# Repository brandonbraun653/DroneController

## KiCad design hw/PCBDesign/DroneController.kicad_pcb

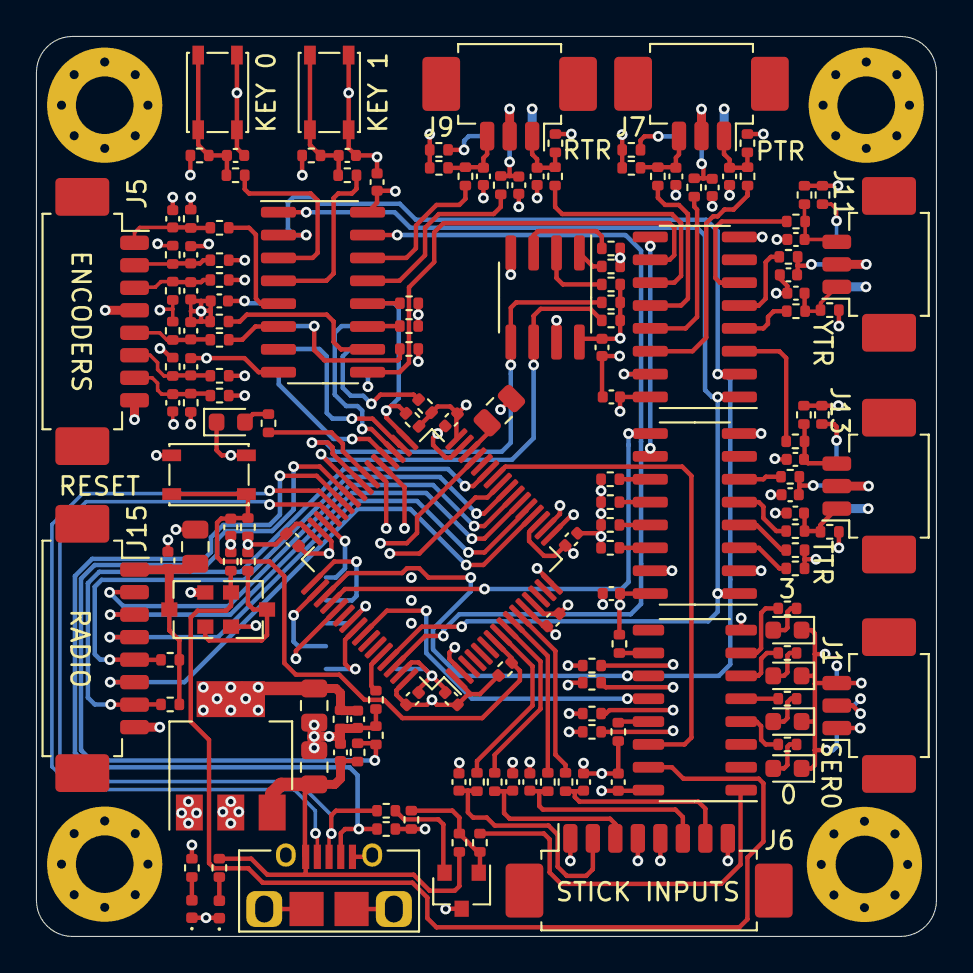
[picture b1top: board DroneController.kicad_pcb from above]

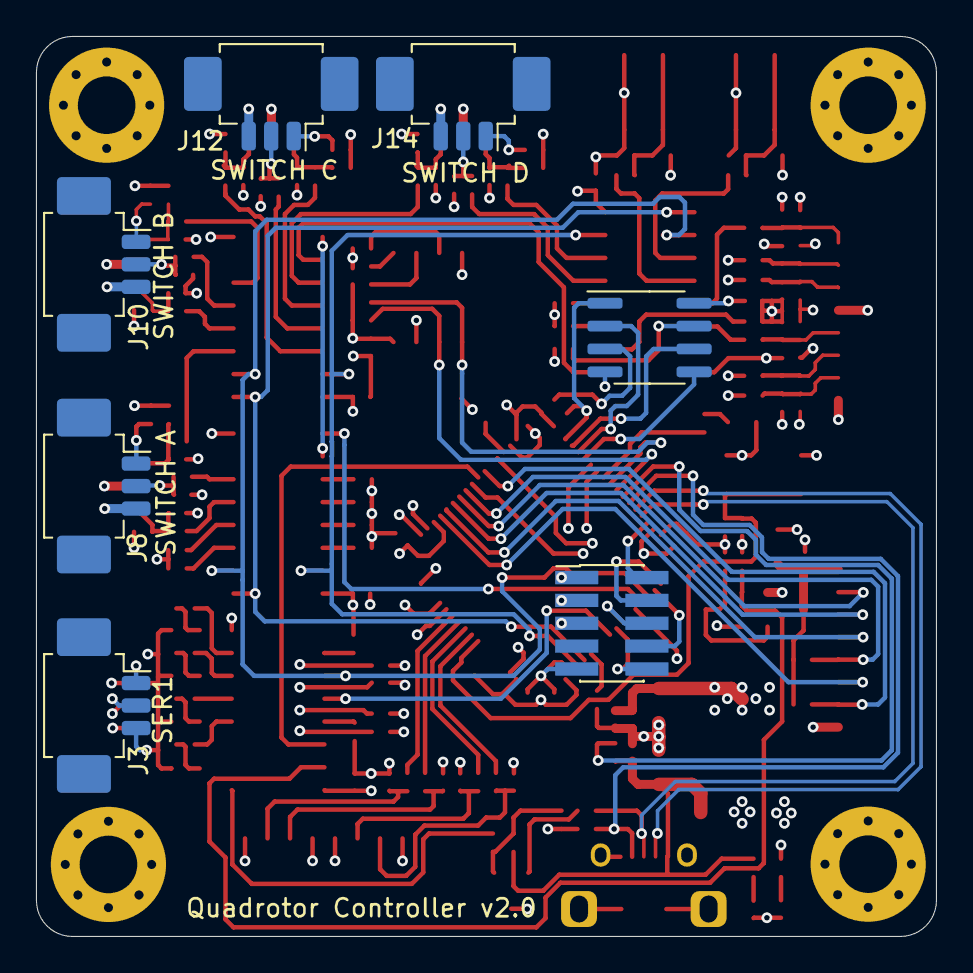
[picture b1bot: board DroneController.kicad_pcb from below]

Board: 4 copper layers, 50.0 x 50.0 mm, 173 parts (7 on the bottom side), 129 nets.

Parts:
C1, C2, C3, C10, C11, C12, C13, C14, C15, C16, C17, C18, C19, C20, C21, C26, C27, C28, C29, C30, C31, C32, C33, C35, C37, C47, C50, C55, C56, C57: 100n; C_0402_1005Metric
C4, C5, C6, C7, C8, C9, C22, C23, C24, C25: 10n; C_0402_1005Metric
C34: 10uF; C_0805_2012Metric
C41, C44: 1uF; C_0805_2012Metric
C52: 2.2uF; C_0805_2012Metric
D1: DBG_LED_0; LED_0603_1608Metric
D3: STATUS_LED; LED_0603_1608Metric
D4: DBG_LED_3; LED_0603_1608Metric
D5: DBG_LED_2; LED_0603_1608Metric
D6: DBG_LED_1; LED_0603_1608Metric
D8: LED_5V0; LED_0402_1005Metric
D9: LED_3V3; LED_0402_1005Metric
H1, H2, H3, H4: MountingHole_Pad; MountingHole_3.2mm_M3_Pad_Via
J1, J3: SerialDebug; Molex_PicoBlade_53261-0371_1x03-1MP_P1.25mm_Horizontal
J2: USB_B_Micro; Amphenol-MicroB
J4: Conn_ARM_JTAG_SWD_10; PinHeader_2x05_P1.27mm_Vertical_SMD
J5: EncoderConn; Molex_PicoBlade_53261-0871_1x08-1MP_P1.25mm_Horizontal
J6: JoystickConn; Molex_PicoBlade_53261-0871_1x08-1MP_P1.25mm_Horizontal
J7: PTrim; Molex_PicoBlade_53261-0371_1x03-1MP_P1.25mm_Horizontal
J8: SW_A; Molex_PicoBlade_53261-0371_1x03-1MP_P1.25mm_Horizontal
J9: RTrim; Molex_PicoBlade_53261-0371_1x03-1MP_P1.25mm_Horizontal
J10: SW_B; Molex_PicoBlade_53261-0371_1x03-1MP_P1.25mm_Horizontal
J11: YTrim; Molex_PicoBlade_53261-0371_1x03-1MP_P1.25mm_Horizontal
J12: SW_C; Molex_PicoBlade_53261-0371_1x03-1MP_P1.25mm_Horizontal
J13: TTrim; Molex_PicoBlade_53261-0371_1x03-1MP_P1.25mm_Horizontal
J14: SW_D; Molex_PicoBlade_53261-0371_1x03-1MP_P1.25mm_Horizontal
J15: Conn_01x08; Molex_PicoBlade_53261-0871_1x08-1MP_P1.25mm_Horizontal
Q2: MMBT3904; SOT-23
Q3: 2N7002; SOT-23
Q5: LBSS84LT1G; SOT-23
R1, R2, R7, R8, R9, R10, R11, R12, R15, R17, R20, R22, R23, R24, R28, R29, R30, R34, R35, R36, R45, R46, R47, R49, R50, R51, R52, R53, R54, R57, R58, R59, R61, R62, R64, R65, R66, R67, R70, R71, R72, R74, R85, R88, R89, R90, R91, R96, R97, R98, R99: 10k; R_0402_1005Metric
R3, R4, R5, R6, R13, R14, R16, R18, R19, R21, R25, R26, R27, R31, R32, R33, R37, R38, R39, R40, R41, R42, R48, R55: 1k; R_0402_1005Metric
R56, R92, R93, R94, R95: 560; R_0402_1005Metric
R60, R68, R69, R75: 1.5k; R_0402_1005Metric
R63: 330; R_0402_1005Metric
R73: 5.1k; R_0402_1005Metric
R76: 4.7k; R_0402_1005Metric
R77: 33k; R_0402_1005Metric
R78: 100; R_0402_1005Metric
SW13: Key_User; SW_SPST_PTS810
SW15: Key_nRESET; SW_SPST_PTS810
SW17: Key_nBOOT; SW_SPST_PTS810
U1, U2, U3: 74HC165; SOIC-16_3.9x9.9mm_P1.27mm
U4: AT25SF081; SOIC-8_3.9x4.9mm_P1.27mm
U5: AT24C256; SOIC-8_3.9x4.9mm_P1.27mm
U8: AMS1117-3.3; SOT-223-3_TabPin2
U11: 74HC595; SO-16_3.9x9.9mm_P1.27mm
U13: STM32F446RETx; LQFP-64_10x10mm_P0.5mm

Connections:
+3V3: C1.1, C2.1, C3.1, C26.1, C27.1, C29.1, C31.1, C33.1, C44.1, C47.1, C50.1, C55.1, C56.1, C57.1, J4.1, J6.1, J6.5, Q2.3, Q5.2, R7.1, R8.2, R9.1, R10.2, R11.1, R12.1, R15.1, R17.1, R20.1, R22.1, R23.1, R24.1, R28.1, R29.1, R30.1, R34.1, R35.1, R36.1, R50.1, R53.1, R57.1, R62.1, R63.2, R64.1, R67.1, R68.1, R69.1, R85.1, R88.2, R97.2, R98.2, R99.1, U1.16, U2.16, U3.16, U4.8, U5.8, U8.2, U11.16, U13.1, U13.13, U13.19, U13.32, U13.48, U13.64
+5V: C37.1, C41.2, J2.1, R60.2, R73.2, R76.2, U8.3
/Human Machine Interface/ENC0_A: R5.2, U13.53
/Human Machine Interface/ENC0_B: R6.2, U13.2
/Human Machine Interface/ENC1_A: R3.2, U13.16
/Human Machine Interface/ENC1_B: R4.2, U13.17
/Human Machine Interface/Joy Stick Inputs/JS_0: C25.1, J6.2, R42.1
/Human Machine Interface/Joy Stick Inputs/JS_1: C24.1, J6.3, R41.2
/Human Machine Interface/Joy Stick Inputs/JS_2: C23.1, J6.6, R40.1
/Human Machine Interface/Joy Stick Inputs/JS_3: C22.1, J6.7, R39.2
/Human Machine Interface/KEY_MISO: U1.9, U13.52
/Human Machine Interface/KEY_SCK: U1.2, U2.2, U3.2, U11.11, U13.51
/Human Machine Interface/KEY_nCS: U1.15, U2.15, U3.15, U13.62
/Human Machine Interface/KEY_nSAMPLE: U1.1, U2.1, U3.1, U13.61
/Human Machine Interface/Rotary Encoder/SW1_A: C4.2, J5.2, R3.1, R7.2
/Human Machine Interface/Rotary Encoder/SW1_B: C5.1, J5.3, R4.1, R8.1
/Human Machine Interface/Rotary Encoder/SW1_Btn: C8.1, J5.1, R11.2, R13.2
/Human Machine Interface/Rotary Encoder/SW2_A: C6.2, J5.6, R5.1, R9.2
/Human Machine Interface/Rotary Encoder/SW2_B: C7.1, J5.7, R6.1, R10.1
/Human Machine Interface/Rotary Encoder/SW2_Btn: C9.1, J5.5, R12.2, R14.2
/Human Machine Interface/d0: R54.1, U3.11
/Human Machine Interface/d1: R52.1, U3.12
/Human Machine Interface/d2: R33.2, U3.13
/Human Machine Interface/d3: R25.1, U3.14
/Human Machine Interface/d4: R48.2, U3.3
/Human Machine Interface/d5: R55.2, U3.4
/Human Machine Interface/d6: R13.1, U3.5
/Human Machine Interface/d7: R14.1, U3.6
/Human Machine Interface/d8: R26.2, U2.11
/Human Machine Interface/d9: R18.1, U2.12
/Human Machine Interface/d10: R27.2, U2.13
/Human Machine Interface/d11: R19.2, U2.14
/Human Machine Interface/d12: R37.1, U2.3
/Human Machine Interface/d13: R32.2, U2.4
/Human Machine Interface/d14: R21.2, U2.5
/Human Machine Interface/d15: R31.1, U2.6
/Human Machine Interface/d16: R49.1, U1.11
/Human Machine Interface/d17: R2.1, U1.12
/Human Machine Interface/d18: R47.1, U1.13
/Human Machine Interface/d19: R51.1, U1.14
/Human Machine Interface/d20: R46.1, U1.3
/Human Machine Interface/d21: R45.1, U1.4
/Human Machine Interface/d22: R38.2, U1.5
/Human Machine Interface/d23: R16.2, U1.6
/Human Machine Interface/nRESET: C30.2, R53.2, R97.1, SW15.1, U13.7
/Power Supply/USB_D+: J2.3, R75.1, U13.45
/Power Supply/USB_D-: J2.2, U13.44
/Power Supply/USB_ID: J2.4, R72.2, U13.43
/Processor/ANALOG_IN_VPITCH: R40.2, U13.10
/Processor/ANALOG_IN_VROLL: R39.1, U13.11
/Processor/ANALOG_IN_VTHROTTLE: R42.2, U13.8
/Processor/ANALOG_IN_VYAW: R41.1, U13.9
/Processor/DBG_UART_RX_0: J1.2, R89.2
/Processor/DBG_UART_RX_1: J3.2, R59.2
/Processor/DBG_UART_TX_0: J1.1, R91.1
/Processor/DBG_UART_TX_1: J3.1, R65.2
/Processor/EEPROM_SCL: R69.2, U5.6, U13.41
/Processor/EEPROM_SDA: R68.2, U5.5, U13.40
/Processor/JT_TCK: J4.4, U13.49
/Processor/JT_TDI: J4.8, U13.50
/Processor/JT_TDO: J4.6, U13.55
/Processor/JT_TMS: J4.2, U13.46
/Processor/JT_nRST: J4.10, U13.56
/Processor/KEY_MOSI: U11.14, U13.26
/Processor/KeyOut_nCS: U11.12, U13.57
/Processor/NOR_MISO: U4.2, U13.35
/Processor/NOR_MOSI: U4.5, U13.36
/Processor/NOR_SCK: U4.6, U13.34
/Processor/NOR_nCS: R99.2, U4.1, U13.33
/Processor/RF24_CE: J15.6, U13.20
/Processor/RF24_MISO: J15.3, U13.22
/Processor/RF24_MOSI: J15.2, U13.23
/Processor/RF24_SCK: J15.4, U13.21
/Processor/RF24_VCC_EN: Q3.1, R58.2, U11.15
/Processor/RF24_nCS: J15.5, R70.2, U13.24
/Processor/RF24_nIRQ: J15.7, R71.2, U13.27
/Processor/USB_SENSE: R73.1, R74.2, U13.42
/Processor/USB_nRENUMERATE: R78.1, U11.1
GND: C1.2, C2.2, C3.2, C4.1, C5.2, C6.1, C7.2, C8.2, C9.2, C10.2, C11.2, C12.2, C13.2, C14.2, C15.2, C16.2, C17.2, C18.2, C19.2, C20.2, C21.2, C22.2, C23.2, C24.2, C25.2, C26.2, C27.2, C28.1, C29.2, C30.1, C31.2, C32.1, C33.2, C34.2, C35.2, C37.2, C41.1, C44.2, C47.2, C50.2, C52.1, C55.2, C56.2, C57.2, D1.1, D3.1, D4.1, D5.1, D6.1, D8.1, D9.1, H1.1, H2.1, H3.1, H4.1, J1.3, J2.5, J3.3, J4.3, J4.5, J4.9, J5.4, J5.8, J6.4, J6.8, J7.2, J8.3, J9.2, J10.3, J11.2, J12.3, J13.2, J14.3, J15.8, Q3.2, R1.2, R2.2, R45.2, R46.2, R47.2, R49.2, R51.2, R52.2, R54.2, R58.1, R61.2, R66.1, R72.1, R74.1, R77.1, R85.2, R90.1, R96.2, SW13.2, SW15.2, SW17.2, U1.8, U2.8, U3.8, U4.4, U5.4, U5.7, U8.1, U11.8, U13.12, U13.18, U13.31, U13.47, U13.63
unnamed: C10.1, J7.3, R15.2, R18.2
unnamed: C11.1, J8.2, R16.1
unnamed: C12.1, J7.1, R17.2, R19.1
unnamed: C13.1, J9.3, R22.2, R25.2
unnamed: C14.1, J10.2, R21.1
unnamed: C15.1, J9.1, R23.2, R26.1
unnamed: C16.1, J11.3, R28.2, R31.2
unnamed: C17.1, J12.2, R27.1
unnamed: C18.1, J11.1, R29.2, R32.1
unnamed: C19.1, J13.3, R34.2, R37.2
unnamed: C20.1, J14.2, R33.1
unnamed: C21.1, J13.1, R35.2, R38.1
unnamed: C28.2, R48.1, R50.2, SW13.1
unnamed: C32.2, R55.1, R57.2, SW17.1
unnamed: C34.1, C35.1, J15.1, Q5.3, R70.1, R71.1
unnamed: C52.2, U13.30
unnamed: D1.2, R56.1
unnamed: D3.2, R92.1
unnamed: D4.2, R93.1
unnamed: D5.2, R94.1
unnamed: D6.2, R95.1
unnamed: D8.2, R60.1
unnamed: D9.2, R63.1
unnamed: J8.1, R20.2
unnamed: J10.1, R24.2
unnamed: J12.1, R30.2
unnamed: J14.1, R36.2
unnamed: Q2.1, R76.1, R77.2, R78.2
unnamed: Q2.2, R75.2
unnamed: Q3.3, Q5.1, R98.1
unnamed: R1.1, U3.10
unnamed: R56.2, U11.4
unnamed: R59.1, U13.38
unnamed: R61.1, U5.3
unnamed: R62.2, U5.2
unnamed: R64.2, U4.7
unnamed: R65.1, U13.37
unnamed: R66.2, U5.1
unnamed: R67.2, U4.3
unnamed: R88.1, U11.10
unnamed: R89.1, U13.25
unnamed: R90.2, U11.13
unnamed: R91.2, U13.29
unnamed: R92.2, U13.39
unnamed: R93.2, U11.7
unnamed: R94.2, U11.6
unnamed: R95.2, U11.5
unnamed: R96.1, U13.60
unnamed: U1.10, U2.9
unnamed: U2.10, U3.9

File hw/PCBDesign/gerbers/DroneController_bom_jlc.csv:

"Comment","Designator","Footprint","LCSC Part #"
"100n","C3,C1,C2,C10,C12,C13,C15,C16,C18,C19,C21,C11,C14,C17,C20,C28,C30,C32,C26,C27,C35,C58,C47,C37,C40,C50,C55,C56,C57,C33,C31,C29","C_0402_1005Metric","C1525"
"10n","C8,C5,C4,C9,C7,C6,C23,C22,C25,C24","C_0402_1005Metric","C15195"
"10uF","C34,C59","C_0805_2012Metric","C28323"
"4.7uF","C38","C_0805_2012Metric","C1779"
"1uF","C44,C41,C36","C_0805_2012Metric","C28323"
"2.2uF","C52","C_0805_2012Metric","C49217"
"1.5pF","C53,C54","C_0402_1005Metric","C1552"
"LED_PGD","D1","LED_0402_1005Metric","C72043"
"LED_CHG","D2","LED_0402_1005Metric","C2286"
"STATUS_LED","D3","LED_0603_1608Metric","C72041"
"DBG_LED_2","D4","LED_0603_1608Metric","C72041"
"DBG_LED_1","D5","LED_0603_1608Metric","C72041"
"DBG_LED_0","D6","LED_0603_1608Metric","C72041"
"BT_ON","D7","LED_0603_1608Metric","C72041"
"LED_5V0","D8","LED_0402_1005Metric","C72043"
"LED_3V3","D9","LED_0402_1005Metric","C72041"
"MMBT3904","Q1","SOT-23","C20526"
"2N7002","Q2,Q3","SOT-23","C8545"
"LBSS84LT1G","Q4,Q5","SOT-23","C8492"
"10k","R1,R2,R45,R46,R47,R49,R51,R11,R7,R8,R12,R9,R10,R15,R17,R22,R23,R28,R29,R34,R35,R20,R24,R30,R36,R50,R53,R57,R62,R66,R61,R67,R64,R99,R71,R70,R98,R58,R59,R56,R100,R85,R79,R96,R97,R90,R88,R65,R91,R89","R_0402_1005Metric","C25744"
"1k","R13,R3,R4,R14,R5,R6,R18,R19,R25,R26,R31,R32,R37,R38,R16,R21,R27,R33,R40,R39,R42,R41,R44,R48,R55","R_0402_1005Metric","C11702"
"100","R43","R_0402_1005Metric","C25076"
"33","R52,R54","R_0402_1005Metric","C25105"
"330","R63","R_0402_1005Metric","C25104"
"1.5k","R68,R69,R80,R81,R60","R_0402_1005Metric","C25867"
"100k","R83,R82,R73,R84","R_0402_1005Metric","C25741"
"0","R87,R86","R_0805_2012Metric","C17477"
"560","R101,R93,R94,R95,R92","R_0402_1005Metric","C11702"
"74HC165","U3,U1,U2","SOIC-16_3.9x9.9mm_P1.27mm","C5613"
"AT24C256","U5","SOIC-8_3.9x4.9mm_P1.27mm","C6482"
"TP4056","U7","TP4056_SOP-8-PP","C16581"
"AMS1117-3.3","U8","SOT-223-3_TabPin2","C6186"
"74HC595","U11","SO-16_3.9x9.9mm_P1.27mm","C5947"
"STM32F446RETx","U13","LQFP-64_10x10mm_P0.5mm","C69336"
"8MHz Crystal","Y1","Crystal_SMD_5032-2Pin_5.0x3.2mm","C115962"

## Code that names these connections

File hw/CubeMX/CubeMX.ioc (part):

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Mcu.Name=STM32F446R(C-E)Tx
Mcu.Package=LQFP64
Mcu.UserName=STM32F446RETx
PA0-WKUP.Signal=ADCx_IN0
PA1.Signal=ADCx_IN1
PA10.GPIOParameters=GPIO_Label
PA10.GPIO_Label=Encoder1_A
PA10.Signal=GPXTI10
PA11.Mode=Device_Only
PA11.Signal=USB_OTG_FS_DM
PA12.Mode=Device_Only
PA12.Signal=USB_OTG_FS_DP
PA13.Mode=JTAG_5_pins
PA13.Signal=SYS_JTMS-SWDIO
PA14.Mode=JTAG_5_pins
PA14.Signal=SYS_JTCK-SWCLK
PA15.Mode=JTAG_5_pins
PA15.Signal=SYS_JTDI
PA2.Signal=ADCx_IN2
PA3.Signal=ADCx_IN3
PA4.GPIOParameters=GPIO_Label
PA4.GPIO_Label=RF24_CE
PA4.Signal=GPIO_Output
PA5.Mode=Full_Duplex_Master
PA5.Signal=SPI1_SCK
PA6.Mode=Full_Duplex_Master
PA6.Signal=SPI1_MISO
PA7.Mode=Full_Duplex_Master
PA7.Signal=SPI1_MOSI
PA8.Mode=I2C
PA8.Signal=I2C3_SCL
PA9.GPIOParameters=GPIO_Label
PA9.GPIO_Label=Encoder1_B
PA9.Signal=GPIO_Input
PB0.Mode=Full_Duplex_Master
PB0.Signal=SPI3_MOSI
PB1.GPIOParameters=GPIO_Label
PB1.GPIO_Label=RF24_IRQ
PB1.Signal=GPXTI1
PB10.GPIOParameters=GPIO_Label
PB10.GPIO_Label=USART3_DBG_TX
PB10.Mode=Asynchronous
PB10.Signal=USART3_TX
PB12.GPIOParameters=GPIO_Label
PB12.GPIO_Label=NOR_CSm
PB12.Signal=GPIO_Output
PB13.Mode=Full_Duplex_Master
PB13.Signal=SPI2_SCK
PB14.Mode=Full_Duplex_Master
PB14.Signal=SPI2_MISO
PB15.Mode=Full_Duplex_Master
PB15.Signal=SPI2_MOSI
PB3.Mode=JTAG_5_pins
PB3.Signal=SYS_JTDO-SWO
PB4.Mode=JTAG_5_pins
PB4.Signal=SYS_JTRST
PB5.GPIOParameters=GPIO_Label
PB5.GPIO_Label=KeyOut_nCS
PB5.Signal=GPIO_Output
PB6.Signal=S_TIM4_CH1
PB7.Signal=S_TIM4_CH2
PB8.GPIOParameters=GPIO_Label
PB8.GPIO_Label=Key_nSample
PB8.Signal=GPIO_Output
PB9.GPIOParameters=GPIO_Label
PB9.GPIO_Label=Key_nCS
PB9.Signal=GPIO_Output
PC0.Signal=ADCx_IN10
PC1.Signal=ADCx_IN11
PC10.Mode=Full_Duplex_Master
PC10.Signal=SPI3_SCK
PC11.Mode=Full_Duplex_Master
PC11.Signal=SPI3_MISO
PC12.GPIOParameters=GPIO_Label
PC12.GPIO_Label=Encoder0_B
PC12.Signal=GPIO_Input
PC2.Signal=ADCx_IN12
PC3.Signal=ADCx_IN13
PC4.GPIOParameters=GPIO_Label
PC4.GPIO_Label=RF24_CS
PC4.Signal=GPIO_Output
PC5.GPIOParameters=GPIO_Label
PC5.GPIO_Label=USART3_DBG_RX
PC5.Mode=Asynchronous
PC5.Signal=USART3_RX
PC6.GPIOParameters=GPIO_Label
PC6.GPIO_Label=USART6_BT_TX
PC6.Mode=Asynchronous
PC6.Signal=USART6_TX
PC7.GPIOParameters=GPIO_Label
PC7.GPIO_Label=USART6_BT_RX
PC7.Mode=Asynchronous
PC7.Signal=USART6_RX
PC8.GPIOParameters=GPIO_Label
PC8.GPIO_Label=BT_IRQ
PC8.Signal=GPXTI8
PC9.Mode=I2C
PC9.Signal=I2C3_SDA
PD2.GPIOParameters=GPIO_Label
PD2.GPIO_Label=Encoder0_A
PD2.Signal=GPXTI2
PH0-OSC_IN.Mode=HSE-External-Oscillator
PH0-OSC_IN.Signal=RCC_OSC_IN
PH1-OSC_OUT.Mode=HSE-External-Oscillator
PH1-OSC_OUT.Signal=RCC_OSC_OUT
board=custom

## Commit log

2020-12-17 Added core driver libraries
2020-12-18 Bring up heartbeat and watchdog tasks
2020-12-19 Pull up submodules to integrate build system updates
2020-12-19 Pull up submodules
2020-12-20 Semi-configured and untested uGFX building
2020-12-21 Integrated uGFX with the ST7735 driver
2020-12-22 Added Ripple submodule
2020-12-23 Enabled WWDG in Thor config. Pull up submodules
2020-12-24 Add hardware watchdog timeout integration
2020-12-24 Tested hardware watchdog in system
2020-12-29 Added thread for radio link. Started integration tasks
2020-12-30 Add skeleton for project specific networking driver
2020-12-30 Redirected the initialization sequence to the RF driver
2021-01-01 Submodule updates
2021-01-02 Test out handler for TX -> MAX_RT fail
2021-01-02 Added test HMI button for triggering packet transfers
2021-01-04 Pull up submodules. Testing out TX
2021-01-05 Working datalink layer
2021-01-07 Pull up submodules. Minor refactoring
2021-01-08 Pull up submodules. Sync for PC
2021-01-09 Added core yaffs integration library
2021-01-09 Weird state
2021-01-09 Actually add the Yaffs source code
2021-01-09 Pull up submodues
2021-01-09 Integration work for Yaffs2, but device doesn't have enough memory
2021-01-09 save work
2021-01-09 Added core yaffs integration library
    Weird state
    Actually add the Yaffs source code
    Pull up submodues
    Resolve merge conflict
2021-01-10 Compiling with LittleFS enabled
2021-01-10 Implement memory minimization through removal of virtual inheritance
2021-01-10 Update build system
2021-01-10 Removed all shared_ptr interfaces to HW drivers
2021-01-11 Pull up submodules for starting F4 dev work
2021-01-11 Pull up submodules. More integration of F4 drivers
2021-01-12 Test out new RCC driver model
2021-01-12 Pull up submodules. Created common project settings for the workspace
2021-01-15 Pull up submodules. Interrupt callback registry tests
2021-01-18 sync for pc
2021-01-23 Submodule update
2021-01-25 Update submodules
2021-01-25 Pull up submodules. Enable SPI driver
2021-01-26 Update gitignore
2021-01-29 Pull up submodules. Working F4 SPI
2021-01-29 Got the LCD working on the F4
2021-01-29 Rework the initialization structure
2021-01-30 Update build system to account for database
2021-01-31 Pull up submodules. Integrate first cut of database/datastore
2021-02-02 Work on screen setup
2021-02-05 Pull up submodules. Test out button sense
2021-02-06 Validate rotary encoder inputs
2021-02-06 Add better startup to registry
2021-02-07 Add more registry improvements
2021-02-08 Compile and debug simulator target. Not actually functioning yet.
2021-02-09 Compile source code under embedded and sim target
2021-02-10 Get the simulator to start all threads
2021-02-11 Refactor threading
2021-02-13 Simulator threads booting properly now
2021-02-13 Working virtual GPIO driver
2021-02-14 Added a proper filesystem indirection. Integrated the console logger for simulator
2021-02-14 Reworked the registry and filesystem to be closer to production interfaces
2021-02-14 Integrated virtual SPI driver. Removed accidental binary tracking
2021-02-16 Tested out some very basic ZeroMQ transport functionality on ChimeraSim
2021-02-16 Removed accidental tracking of PyCharm project
2021-02-18 Working networked SPI sim driver
2021-02-19 Turn back on radio with initial virtual driver stubs
2021-02-20 Get the millis functionality working
2021-02-21 Start working on new network driver approach
2021-02-21 Refactored driver working on sim again
2021-02-21 Use static thread allocation on network driver
2021-02-23 Pull up submodules. Fix thread lock on tx
2021-02-27 Single transmit + ACK from simulator
2021-03-03 Simple test for fragmented packet transmission
2021-03-07 Add initial PCB project
2021-03-07 Fill out a lot of the board schematic
2021-03-08 Save
2021-03-09 Add HMI input circuitry
2021-03-09 Routed JTAG and power to the processor
2021-03-09 Planned out some of the system level connections on the processor IO
2021-03-10 Wire some of the protocols
2021-03-10 Finished initial schematic design
2021-03-11 Clean up schematics some
2021-03-11 Schematic polishing
2021-03-13 Added PCB
2021-03-13 Added NanoPB submodule
2021-03-13 Compile protobuf
2021-03-13 Remove botched submodule add
2021-03-13 Re-add submodule
2021-03-14 Add shell
2021-03-15 Pull up submodules. Add helper tasks
2021-03-17 Update pcb
2021-03-18 Laid out power section
2021-03-20 Lay out more PCB
2021-03-20 Routed most of the core peripherals
2021-03-21 Complete route of draft #1 finished
2021-03-25 Finished preliminary route of PCB after design review checklist
2021-03-25 Integrate Segger System View
2021-03-26 Adjust components for lowest build cost
2021-03-26 Moved the segger tooling into the Aurora submodule
2021-03-26 Add the JLink logger as a sink
2021-03-27 HW updates. Testing out SPIFFS
2021-03-27 Spiffs somewhat working. Waiting until real dev hardware comes in to pursue this further.
2021-04-17 Add Black Magic Probe debugger support for HW rev 1
2021-04-18 The hardware lives! An LED will blink...
2021-04-20 Clean up the build system and remove unneeded files
2021-04-20 Remove graphics thread. Map some of the HW IO
2021-04-21 Write a simple shift register driver to control output pins
2021-04-22 Add full pin map
2021-04-22 Verified SPI interface to NRF24 on dev hardware
2021-04-22 Add test for SPI flash read/write
2021-04-24 NOR driver improvements
2021-04-24 Address compiler warnings
2021-04-24 Pull up submodules to get working filesystem
2021-04-25 Update the boot count file tracking to use the new Aurora binary file driver
2021-04-25 Remove unused submodules
2021-04-25 Remove another unused submodule
2021-04-26 Sync
2021-04-26 Update the ETL library
2021-04-26 Removed boost
2021-04-26 Add versioning file
2021-04-26 Add back FindBoost so cpputest can compile (not embedded)
2021-04-27 Pull up submodules. Commits remove wasteful memory usage
2021-04-28 Add tinyusb and get it to compile
2021-04-28 Clean up Ripple and add a task for the USB thread
2021-04-28 Add default (empty) implementations of TinyUSB callbacks
2021-04-30 Add configuration of the ADC inputs (untested)
2021-05-01 Re-integrate Segger SysView. Try out ADC single channel capture (not working)
2021-05-01 Single channel conversion working
2021-05-01 Demonstrate streaming of P/R/Y/T ADC input data to registry
2021-05-02 Pull up submodules. Update intellisense settings
2021-05-09 Test out memory to memory DMA transfers
2021-05-14 Fix DMA based serial transmit
2021-05-21 Add some prototype files for the RN4871 driver
2021-05-21 Initialize the Bluetooth serial communications channel
2021-05-22 Print Bluetooth version string and implement commanded reboot
2021-05-22 Add command to set device name
2021-05-22 Add more commands to BT driver. Difficulty parsing right now.
2021-05-23 Add test plate file for F360
2021-05-24 Start work on shift register IO debouncer
2021-05-26 Working event based rotary encoder setup
2021-05-26 Working single key debouncing
2021-05-28 GPIO/Encoder hw event input processing fully running
2021-05-28 Updated the encoder processing
2021-05-29 Sync for laptop work
2021-05-30 ADC driver fully working
2021-05-31 Set up network stack for low level network testing
2021-06-06 Updates to allow simulator to run again
2021-06-09 Add sorting algorithm
2021-06-13 Test out simulator loopback adapter
2021-06-14 Testing on hw...
2021-06-16 Begin work on transition to managed memory network driver
2021-06-21 More updates
2021-06-26 Simple loopback transfer working with dynamic allocation
2021-06-26 Can pump data at high rates on the sim, but I seem to have a thread sync issue
2021-07-10 Added more robust loopback testing on simulator
2021-07-10 Finally! A working hardware net stack! Raw packets being sent wirelessly
2021-07-10 Start working on USB device driver support
2021-07-11 Investigate some USB issues. Add PCB remarks for revision 2
2021-07-17 Process discretes through observable system
2021-07-17 Switch HW drivers to release builds. Pull up submodules.
2021-07-17 Route encoder rotation events through observables
2021-07-17 Integrate new protobuf definitions
2021-08-03 Update networking to use protocol buffers
2021-08-07 Update networking interfaces
2021-08-11 Test packet TX from defs
2021-08-12 Transmit and receive on sim using packet IDs
2021-08-12 Address build issues for embedded target
2021-08-14 Finally got packets fully transmitting on HW
2021-08-14 Increment version
2021-09-28 Update workspace
2021-10-10 Save work on improvements to the bluetooth module drivers
2021-10-11 Add some processing to the manager
2021-10-15 Debug bluetooth module communication issues
2021-10-16 Expand task priorities to be more dynamic
2021-10-17 Working command mode for RN4871
2021-10-23 Functioning BT configuration. Back to par...
2021-10-23 Add generic function to handle BT command mode transactions
2021-10-24 Make bluetooth initialization a little more robust
2021-10-24 Improve documentation
2021-11-27 Make note about USB hardware
2021-12-13 Improve the networking stability of RF24
2021-12-19 Improve networking driver performance
2021-12-20 Improve network driver
2021-12-21 Increase transfer speed
2021-12-22 Start working on PCB rev 2.0
2021-12-22 Add more work on PCB v2 design
2021-12-27 Work further on v2.0 of controller pcb
2021-12-27 Improve PCB design
2021-12-30 Work on adding the i2c driver
2021-12-30 Add more of the I2C driver
2021-12-31 Finish first draft of v2.0 pcb
2022-01-01 Update I2C driver
2022-01-02 Improve i2c driver
2022-01-06 Stall work on I2C driver. EEPROM unresponsive.
2022-01-09 Start adding business logic to propagate controller events through the network.
2022-01-10 Switch to release builds for the submodules
